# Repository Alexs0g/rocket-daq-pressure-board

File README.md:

# rocket-daq-pressure-board

PCB design project from Purdue Orbital's propulsion electronics subteam (Spring 2025),
continued independently. A pressure sensor board for the data acquisition system used
in solid rocket motor testing.

## Contents
- [v1 Design Overview](docs/v1-design-overview.pdf) – the board I designed for the team
- v1 KiCad files: `hardware/v1/`
- [v1 Requirements Gap Analysis](docs/v1-requirements-gap.pdf) – what the test needed vs. what v1 can do
- v1 build and test results – coming
- v2 design – coming

## Tools
KiCad, Arduino, Python

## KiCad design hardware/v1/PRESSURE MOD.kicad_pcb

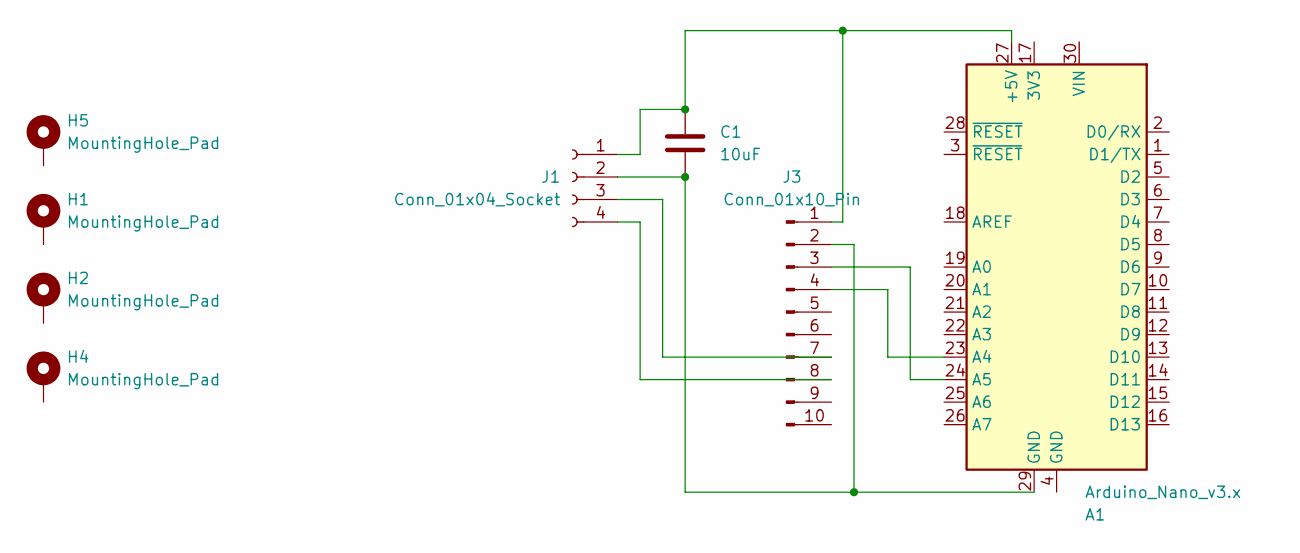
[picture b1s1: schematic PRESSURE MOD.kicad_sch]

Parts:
A1: Arduino_Nano_v3.x; Arduino_Nano
C1: 10uF; CP_Radial_D5.0mm_P2.50mm
H1, H2, H4, H5: MountingHole_Pad; MountingHole_2.5mm_Pad_TopBottom
J1: Conn_01x04_Socket; PinSocket_1x04_P2.54mm_Vertical
J3: Conn_01x10_Pin; PinHeader_1x10_P2.54mm_Vertical

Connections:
unnamed: A1.27 (+5V), C1.1, J1.1, J3.1
unnamed: A1.23 (A4), J3.4
unnamed: A1.24 (A5), J3.3
unnamed: A1.29 (GND), C1.2, J1.2, J3.2
unnamed: J1.3, J3.7
unnamed: J1.4, J3.8

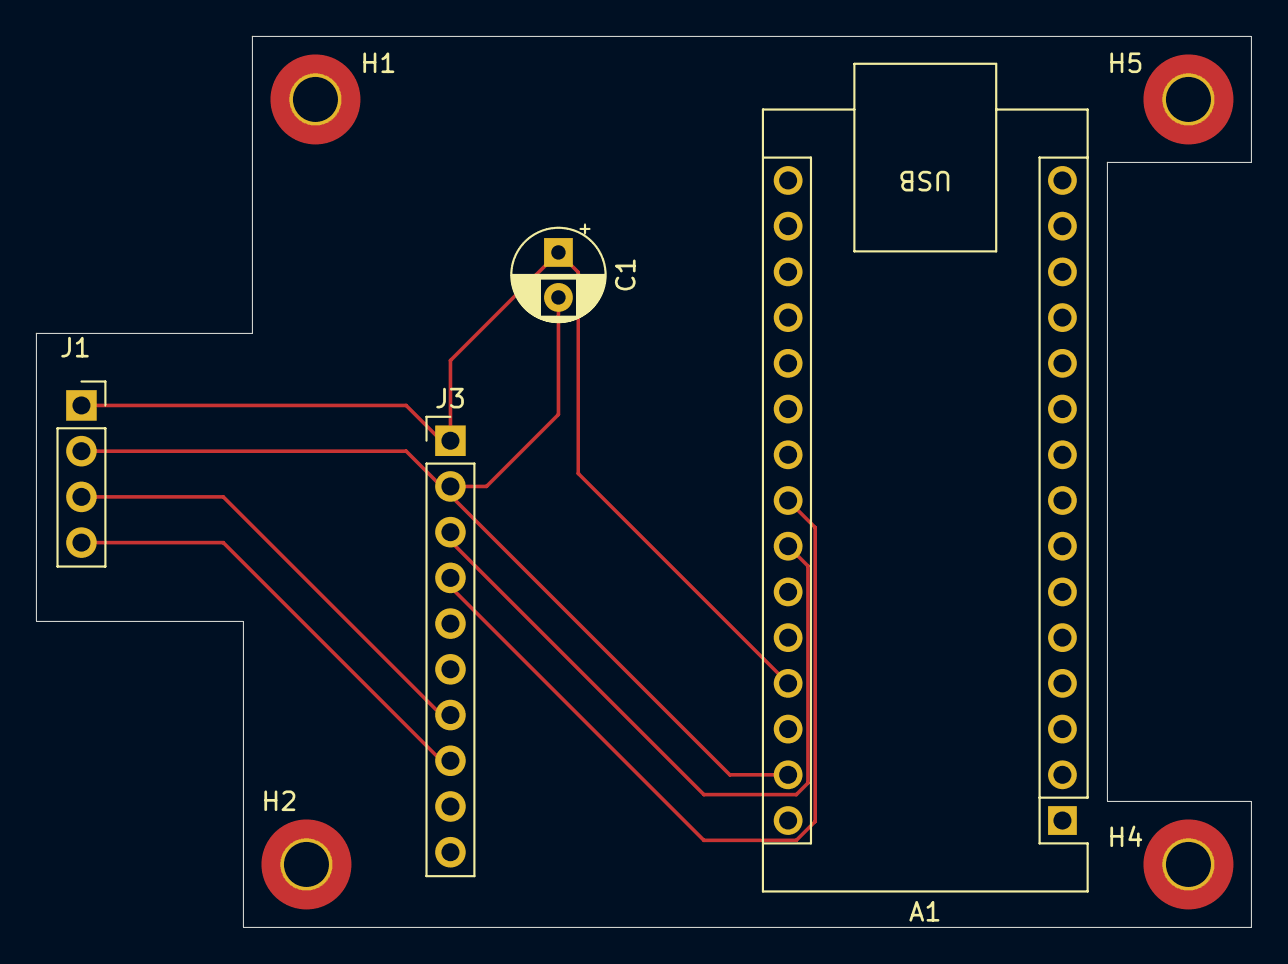
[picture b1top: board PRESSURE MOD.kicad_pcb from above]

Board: 2 copper layers, 67.5 x 49.5 mm, 8 parts (0 on the bottom side), 6 nets.
